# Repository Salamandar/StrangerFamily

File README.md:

# StrangerFamily

A Stranger Things-inspired illuminated alphabet, based on a raspberrypi zero and ws2812B led strips.

## Project structure

* pcb: A RaspberryPi Zero kind-of-HAT with power + LED connectors + level shifter.
* pyStranger: a Python3 project for displaying sentences from a file and/or a keyboard
* StrangerPi: CustomPiOS-based project to generate a raspberry pi imae
* arduinoSerialPixel: experimental "bridge" between raspberry pi and ws2812 leds.

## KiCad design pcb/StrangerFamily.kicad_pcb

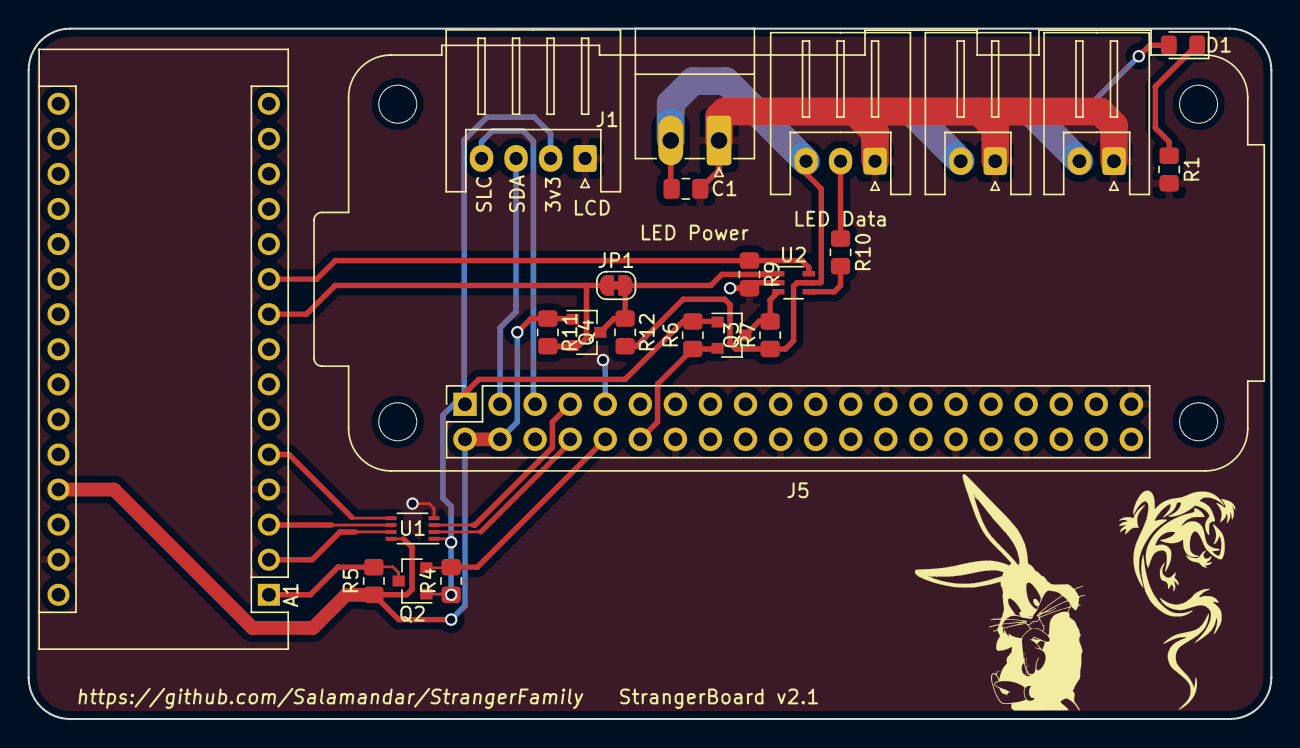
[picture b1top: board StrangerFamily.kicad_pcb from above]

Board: 2 copper layers, 90.0 x 50.0 mm, 24 parts (0 on the bottom side), 21 nets.

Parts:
A1: Arduino_Nano_v3.x; Arduino_Nano
C1: C; C_0805_2012Metric_Pad1.18x1.45mm_HandSolder
D1: D; D_0805_2012Metric_Pad1.15x1.40mm_HandSolder
J1: LCD_Conn; JST_XH_S4B-XH-A_1x04_P2.50mm_Horizontal
J2: Power_LEDs; PhoenixContact_MC_1,5_2-G-3.5_1x02_P3.50mm_Horizontal
J3: Output_LED; JST_XH_S3B-XH-A_1x03_P2.50mm_Horizontal
J4, J6: LED_Out2; JST_XH_S2B-XH-A_1x02_P2.50mm_Horizontal
J5: Raspberry_Pi_zero; Raspberry_Pi_Zero_Socketed_THT_FaceDown_MountingHoles
JP1: Jumper; SolderJumper-2_P1.3mm_Bridged_RoundedPad1.0x1.5mm
Q2, Q3, Q4: BSS138; SOT-23
R1: R; R_0805_2012Metric_Pad1.20x1.40mm_HandSolder
R4, R5, R6, R7, R9, R11, R12: 10k; R_0805_2012Metric_Pad1.20x1.40mm_HandSolder
R10: 470; R_0805_2012Metric_Pad1.20x1.40mm_HandSolder
U1: 74LVC2T45DC; VSSOP-8_2.3x2mm_P0.5mm
U2: 74LVC1G3157; Texas_R-PDSO-G6

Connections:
+3V3: A1.17, J1.2, J5.1, Q2.1, Q3.1, R4.1, R6.1, U1.1
+5V: A1.27, J5.2, J5.4, Q4.1, R5.1, R11.1, U1.8
/Arduino_is_out: A1.10, R9.1, U2.6
/Arduino_out: A1.9, JP1.2, Q4.2, R11.2
/Arduino_out_VDD: JP1.1, Q4.3, R12.2, U2.1
/LCD_SDA: J1.3, J5.3
/LCD_SLC: J1.4, J5.5
/Nano_RX: A1.2, U1.7
/Nano_TX: A1.1, Q2.3, R5.2
/Nano_~Reset: A1.3, U1.6
/PWM0: J5.12, Q3.2, R6.2
/PWM0_VDD: Q3.3, R7.2, U2.3
/RPi_Nano_~Reset: J5.7, U1.3
/RPi_RX: J5.10, Q2.2, R4.2
/RPi_TX: J5.8, U1.2
/RX_enable: A1.5, U1.5
GND: A1.4, A1.29, C1.1, J1.1, J2.1, J3.1, J4.1, J5.6, J5.9, J5.14, J5.20, J5.25, J5.30, J5.34, J5.39, J6.1, R1.2, R9.2, U1.4, U2.2
unnamed: D1.1, R1.1
unnamed: J3.2, R10.1
unnamed: R10.2, U2.4
VCC: C1.2, D1.2, J2.2, J3.3, J4.2, J6.2, R7.1, R12.1, U2.5

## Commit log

2017-12-02 Add script to write archlinux
2017-12-20 Split script into functions. Now, archlinux_prepare_intochroot.sh is to be written.
2017-12-20 cleanup after install
2017-12-20 Add some for install
2017-12-21 First commit of python soft to command the lights
2017-12-21 mount bind the repository inside the chroot
2017-12-21 Split script into functions.
2017-12-21 mount bind is not that great. Just copying, and as read-only.
2017-12-21 Use pushd, add installCode
2017-12-21 add systemd service
2017-12-21 Add default py file
2017-12-21 Add letter lighting python script
2017-12-21 Python3 : fix indent, print()
2017-12-21 Move all strings managemenet to database.py.
2017-12-21 load in constructor. support inexisting file.
2017-12-21 Added some quotes
2017-12-21 Remove header, as it is no more the strandtest
2017-12-21 Add code to get text from keyboard
2017-12-21 Add python-yaml to deps
2017-12-21 Add some to python, thread logic.
2017-12-22 Adding all leds numbers by letter
2017-12-22 Fix imports ; Add dummy Neopixel lib if not found (not on Raspi)
2017-12-22 Static init of list ; fix py3
2017-12-22 Move most global functions to class methods.
2017-12-22 Add leds thread.
2017-12-22 Add LCD interface (no implem yet)
2017-12-22 Small cleanup
2017-12-22 Implementation of "virtual" LCD. LetterLights now updates the LCD.
2017-12-23 Add i2c lcd implementation
2017-12-23 Removed old version of letterLights
2017-12-23 Add dummy version of i2c
2017-12-23 Added .gitignore
2017-12-23 Added permissions to main file
2017-12-23 Fix: if no db found.
2017-12-23 Fix dirname
2017-12-23 Ooops, bad permissions
2017-12-23 Add bash bang to main file
2017-12-23 Fix string concat
2017-12-23 Add do-not-crash-on-i2c-fail test.
2017-12-24 Add debug
2017-12-24 qwerty, correct input device for py
2017-12-24 Fix address for screen
2017-12-24 Add main for test ; fix clear().
2017-12-24 fix env call
2017-12-24 Fix led count
2017-12-24 Changed color eval to hsv
2017-12-24 Fix R led count
2017-12-25 Change leds color definition. Remove verbosity.
2017-12-25 Update service file
2017-12-25 Fix color conversion
2017-12-25 Add animations framework
2017-12-25 oops forgot sleep
2017-12-25 Animations are now strip-agnostic functions
2017-12-25 implement hsv_to_neopixel_color
2017-12-25 Added smooth
2017-12-26 Fix: backspace. Fix test. Fix clean after ok.
2017-12-26 Block for long text, add userfriendly prompt.
2017-12-26 Fix letters count, break sentence on new typed
2017-12-27 Fix hsv_top_neo. Fix smooth animation.
2017-12-27 Added support for progression bar characters
2017-12-27 Fix screen ? Only print keyboard text, cleanup line on print.
2017-12-27 Fix timing for smooth animation
2017-12-28 Dump temp sentences to file
2017-12-28 Add setstringscount
2017-12-28 Implement backing up temp sentences to file
2017-12-28 Fix : load temp on boot, set string count on boot
2017-12-29 Add a "Chenillard" as animation between each sentence
2017-12-29 add ramp to the "Chenillard"
2017-12-29 Fix tabs -> spaces. Fix call.
2017-12-29 Disable string count on screen
2017-12-29 Fix chenillard. Add to sentences loop.
2017-12-29 fix permissions
2017-12-29 tests
2018-03-13 updates during the CCC
2018-06-19 Fix: binfmt was renamed
2018-06-19 Fix: install arch-chroot, update-binfmts inside the script.
2018-06-19 bash…
2018-06-19 Fix: Pacman needs new keys
2018-06-19 Fix when / is not a mountpoint
2018-06-20 add write perms
2018-06-20 add trizen possibility, clearer echo
2018-06-20 Populate pacman-key
2018-06-20 better exit trap
2018-07-10 Add 'true' at the end of "inside script"
2018-07-10 Oops, use first arg of script, not function
2018-08-01 Add hardware, .gitignore updated.
2018-08-01 2 channels, cleanup
2018-08-23 update pacman db before all
2018-08-23 Add LCD connector.
2018-08-24 Use available component on RS
2018-09-20 Change connector footprints (very small non critical changes)
2018-11-02 Huge fix for rsync call
2018-11-02 Add no_copy_script=yes by default
2018-11-02 Cleanup pacman cache before copying
2018-11-14 Fix package names, missing package from image, add compress option
2018-11-17 stupid script for already configured image
2018-11-17 sslverify false for github
2018-11-19 Fix image compression
2018-11-19 Fix ca-certificates error
2020-01-09 Add Pi and Arduino code to control Neopixel Arduino from the Pi
2020-01-09 fix file added
2020-01-10 Simplify call to the Arduino (led per led)
2020-01-13 Écriture de serial.hpp
2020-01-14 update serial speed, start with green and show color on strip after set
2020-01-14 Redirect to fake neopixel lib. Create fake lib init and setPixelColor functions. Need Serial for Python
2020-01-16 Fix method call
2020-01-17 update payload to be b64 arduino reader compliant - not working
2020-01-17 pixel id is an integer - not working
2020-01-25 add method for fake Color class to get RGB values
2020-01-25 use Color object to shutoffLights
2020-01-25 use Color object to last color of chenillard
2020-01-25 Add '=' in the frame sent to serial ; remove serial read
2020-01-25 Update pixel number as it is used with the alphabet
2020-07-15 v2 of hardware with rpi zero w, and arduino nano
2020-11-24 Reorganize arduino code
2020-11-24 Remove unused and legacy scripts
2020-11-24 Add StrangerPi subdirectory, with a CustomPiOS project
2020-11-24 Fix neopixel import
2020-11-24 fix leading spaces
2020-11-25 Update hardware designs. This is v2 sent to prod in august 2020.
2020-11-25 Use apt-get instead of apt. Apt-get keeps packages in cache, not apt.
2020-11-25 Fix raspberry pi missing sd card slot
2020-12-04 Fix electronics (schematics), use new components
2020-12-21 v2 : use logos, move footprints
2020-12-21 update gitignore
2020-12-21 Cleanup, type fixes
2021-02-10 Add script to download raspbian
2021-02-10 Add both arduino variants
2021-02-10 Add github CI for CustomPiOS
2021-02-10 Do not upgrade, it takes a lot of time.
2021-02-10 Update CustomPiOS submodule
2021-02-10 Always upload cache
2021-02-10 use ubuntu-20.04
2021-02-10 Download and cache raspbian image
2021-02-10 Commit image directory with git
2021-02-11 Try to fix github-CI
2021-02-11 Fix path to img
2021-02-11 Reorganize repository
2021-02-11 Move arduino code. Kept named as arduinoSerialPixel because it's not related to the StrangerFamily project
2021-02-11 Change dirs in github ci
2021-02-11 Use actions/cache now
2021-02-11 Rewrite download_raspbian script
2021-02-11 Fix configuration for serial port
2021-02-12 Add arduino_is_out, change start sequence
2021-02-12 Pass baudrate from main
2022-05-29 Bump CustomPiOS version
2022-05-29 Fix build with new custompios, new raspios
2022-06-11 Fix gitignore
2022-06-11 remove vagrant build files
2022-06-11 fix systemd service exec path
2022-06-11 stop using the custompios_path file
2022-06-11 upgrade system
2022-06-11 Define LED_COUNT according to the letters list. Remove one LED from A after repairs.
2022-06-11 Update kicad project version
2022-10-16 Add AtExit code to clean the lights when stopping the script
